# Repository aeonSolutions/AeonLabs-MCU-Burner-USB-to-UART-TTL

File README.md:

[PCB-Prototyping-Catalogue](https://github.com/aeonSolutions/PCB-Prototyping-Catalogue)  >>  [DIY & Maker](https://github.com/aeonSolutions/PCB-Prototyping-Catalogue/blob/main/DIY-Maker/README.md)  >> MCU Burner USB to UART TTL

<p align="right">
 <a href="https://github-com.translate.goog/aeonSolutions/PCB-Prototyping-Catalogue/tree/main?_x_tr_sl=en&_x_tr_tl=pt&_x_tr_hl=en&_x_tr_pto=wapp">Change Language</a> <br>
Last update: 17-2-2024
</p>

<br />

# AeonLabs MCU Burner USB to UART TTL
This repo contains the KiCad files for the micro-USB to UART TTL PCB  or USB to USB for MCUs compatible with direct USB firmware download. This PCB can do firmware download on any AeonLabs PCB designs or any other PCB running at 3.3V or 5.0V.
Features voltage selection : 3.0V 250mA/500mA or 5.0V 500mA and automatic reset and automatic boot. It can fit an enclosure with dimensions of 35x35x4 mm

*Don't forget to LIKE , SHARE and subscribe the free whatsApp group* and if you liked this PCB consider buying me a cup of coffee. Links below.

### Status
 Fully tested and working

<p align="center">
  <br>
 First Firmware download of AeonLabs's USB to UART TTL Burner
 </p>

## Revisions
- revision 1.4
  - added USB to USB option for MCUs compatible with direct USB firmware donwload
- revision 1.x
  - copper track bug corrections  
  - Voltage selection : 3.0V 250mA/500mA or 5.0V 500mA 
  - MCU firmware downloader with automatic reset and automatic boot. 

## Download options
Download this repository if you need the KiCad Files or, download the Gerber files in the release section of this repository

## Liked it ? Get a Free PCB for yourself
Send me your Device or hardware and i will design a custom PCB for it. Free of charge. Contact-me on WhatsApp or email for more info. 

## Q&A WhatsApp Group
If you have any Questions or simply  like this kind of projects and want to stay updated with the latest research ideas and prototypes during the day and week, join the WhatsApp Group
[LDAD Lab & Prototyping](https://chat.whatsapp.com/FkNC7u83kuy2QRA5sqjBVg)

There are useful answers on stackExchage about this topic i recommed reading. One is [ESP-WROOM-32 layout USB-UART](https://electronics.stackexchange.com/questions/429812/esp-wroom-32-layout-usb-uart/601827#601827) and [ESP32 with FTDI programmer](https://electronics.stackexchange.com/questions/448187/esp32-with-ftdi-programmer/601761#601761)

## Fully assembled PCB
### alternatively, and if you do not want to build a PCB by yourself, you can buy here:

The price will be around 30eur plus postage fees.
(I will also deliver the assembled PCB with all the components in place at a fair aditonal cost).
#### Be supportive of my dedication and work towards technology education and buy me a coffee. Link below.

## PCB Parts list
- DC2DC converter HX4002B x2 : https://s.click.aliexpress.com/e/_Ak7IPx
- Capacitor 100nF SMD 1206 : https://s.click.aliexpress.com/e/_AVdmzr
- Capacitor 2.2uF SMD 1206 : https://s.click.aliexpress.com/e/_AVdmzr
- LED SMD 1206 : https://s.click.aliexpress.com/e/_A9THIl
- Resistor SMD 1206 330R : https://s.click.aliexpress.com/e/_A7OXrR
- Programmer Clip : https://s.click.aliexpress.com/e/_A7s5EN
- 6 core wire : https://s.click.aliexpress.com/e/_Atht2d
- Micro USB PCB socket : https://s.click.aliexpress.com/e/_A123KH 

<br />
<br />

## Author

You can get in touch with me on my LinkedIn Profile:

#### Miguel Tomas

You can also follow my GitHub Profile to stay updated about my latest projects: 

<br>

**Hire me** <br>
See [here](https://github.com/aeonSolutions/PCB-Prototyping-Catalogue/wiki/How-to-Hire-AeonLabs) how to hire AeonLabs.

<br>

### Be supportive of my dedication and work towards technology education and buy me a cup of coffee
The PCB design Files I provide here for anyone to use are free. If you like this Smart Device or use it, please consider buying me a cup of coffee, a slice of pizza or a book to help me study, eat and think new PCB design files.

<p align="center">
    
</p>

### Make a donation on PayPal
Make a donation on PayPal and get a TAX refund*.

<p align="center">
    
</p>

### Support all these open hardware projects and become a GitHub sponsor  
Liked any of my PCB KiCad Designs? Help and Support my open work to all by becoming a GitHub sponsor.

<p align="center">

</p>

# 

### License

Before proceeding to download any of AeonLabs software solutions for open-source development and/or PCB hardware electronics development make sure you are choosing the right license for your project. See [AeonLabs Solutions for Open Hardware & Source Development](https://github.com/aeonSolutions/PCB-Prototyping-Catalogue/wiki/AeonLabs-Solutions-for-Open-Hardware-&-Source-Development) for more information.

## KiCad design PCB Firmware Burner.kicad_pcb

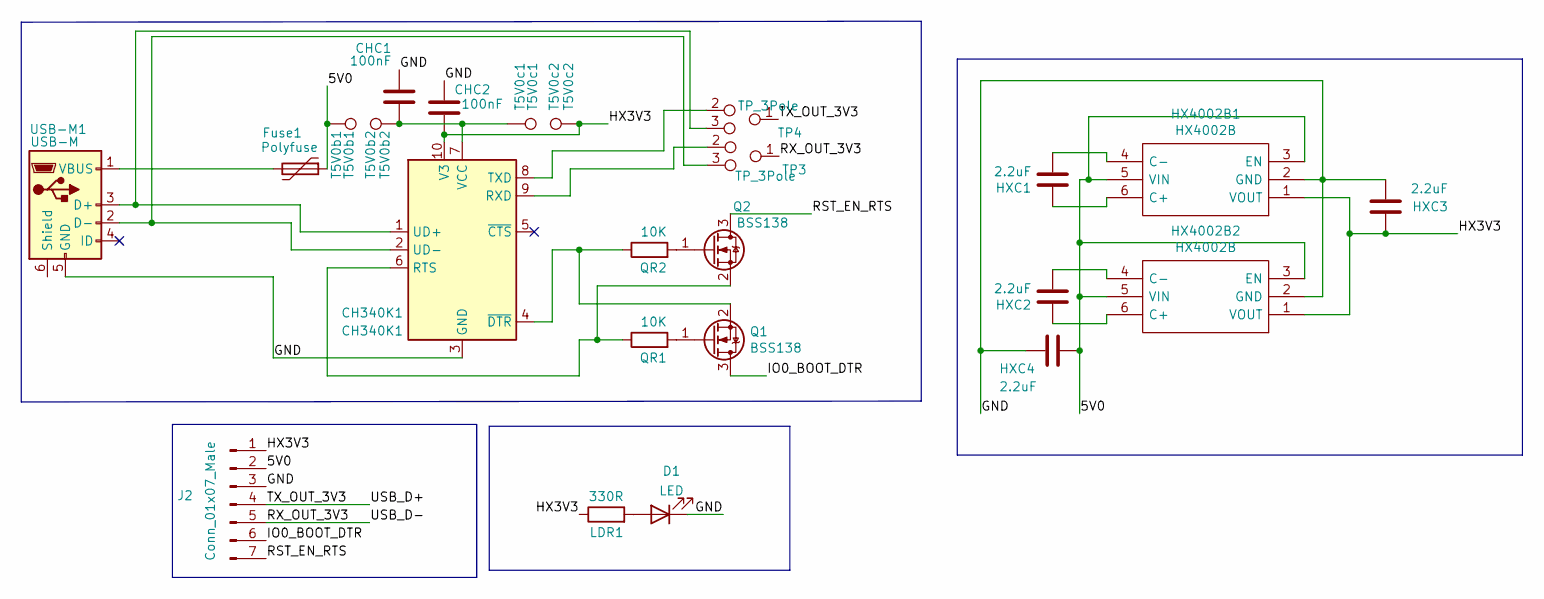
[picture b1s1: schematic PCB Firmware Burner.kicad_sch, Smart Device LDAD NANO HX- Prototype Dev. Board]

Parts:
CH340K1: CH340K1; SSOP-10_3.9x4.9mm_P1.00mm
CHC1, CHC2: 100nF; C_1206_3216Metric
D1: LED; LED_1206_3216Metric
Fuse1: Polyfuse; Fuse_1206_3216Metric
HX4002B1, HX4002B2: HX4002B; HX4002 SOT95 P280X125-6N; Manufacturer_Part_Number HX4002
HXC1, HXC2, HXC3, HXC4: 2.2uF; C_1206_3216Metric
J2: Conn_01x07_Male; PinHeader_1x07_P2.54mm_Horizontal
LDR1: 330R; R_0805_2012Metric_Pad1.20x1.40mm_HandSolder
Q1, Q2: BSS138; SOT-23
QR1, QR2: 10K; R_0805_2012Metric_Pad1.20x1.40mm_HandSolder
T5V0b1: T5V0b1; TestPoint_Pad_2.0x2.0mm
T5V0b2: T5V0b2; TestPoint_Pad_2.0x2.0mm
T5V0c1: T5V0c1; TestPoint_Pad_2.0x2.0mm
T5V0c2: T5V0c2; TestPoint_Pad_2.0x2.0mm
TP3, TP4: TP_3Pole; TestPoint_Pad_1.5mm 3 points
USB-M1: USB-M; Micro_USB_pcb_socket_5pin_4weld_points

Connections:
/5V0: Fuse1.1, HX4002B1.3 (EN), HX4002B1.5 (VIN), HX4002B2.3 (EN), HX4002B2.5 (VIN), HXC4.1, J2.2, T5V0b1.1
/GND: CH340K1.3 (GND), CHC1.2, CHC2.2, D1.1 (K), HX4002B1.2 (GND), HX4002B2.2 (GND), HXC3.2, HXC4.2, J2.3, USB-M1.5 (GND)
/HX3V3: CH340K1.10 (V3), CHC2.1, HX4002B1.1 (VOUT), HX4002B2.1 (VOUT), HXC3.1, J2.1, LDR1.1, T5V0c2.1
/IO0_BOOT_DTR: J2.6, Q1.3 (D)
/RST_EN_RTS: J2.7, Q2.3 (D)
/RX_OUT_3V3: J2.5, TP3.1
/TX_OUT_3V3: J2.4, TP4.1
unnamed: CH340K1.2 (UD-), TP3.3, USB-M1.2 (D-)
unnamed: CH340K1.4 (~DTR), Q1.2 (S), QR2.1
unnamed: CH340K1.6 (RTS), Q2.2 (S), QR1.1
unnamed: CH340K1.7 (VCC), CHC1.1, T5V0b2.1, T5V0c1.1
unnamed: CH340K1.8 (TXD), TP4.2
unnamed: CH340K1.9 (RXD), TP3.2
unnamed: D1.2 (A), LDR1.2
unnamed: Fuse1.2, USB-M1.1 (VBUS)
unnamed: HX4002B1.4 (C-), HXC1.2
unnamed: HX4002B1.6 (C+), HXC1.1
unnamed: HX4002B2.4 (C-), HXC2.2
unnamed: HX4002B2.6 (C+), HXC2.1
unnamed: Q1.1 (G), QR1.2
unnamed: Q2.1 (G), QR2.2
unnamed: CH340K1.1 (UD+), TP4.3, USB-M1.3 (D+)

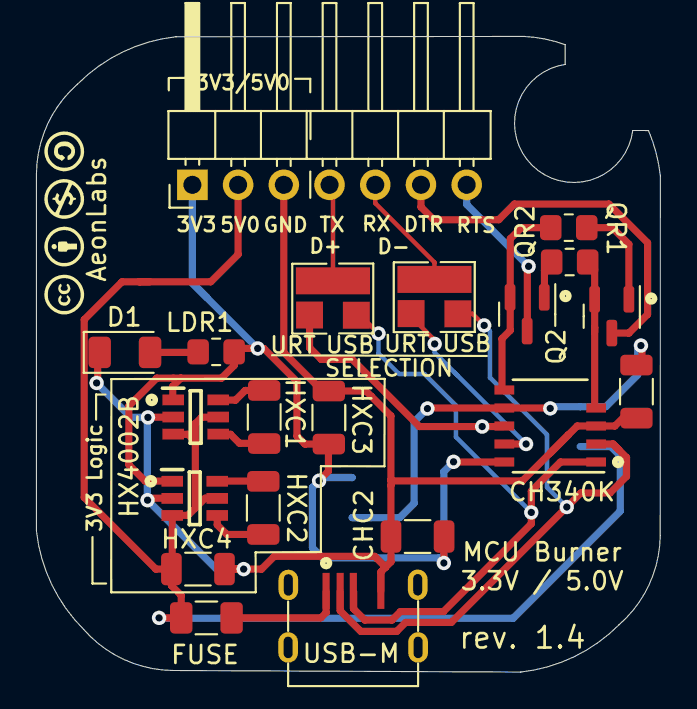
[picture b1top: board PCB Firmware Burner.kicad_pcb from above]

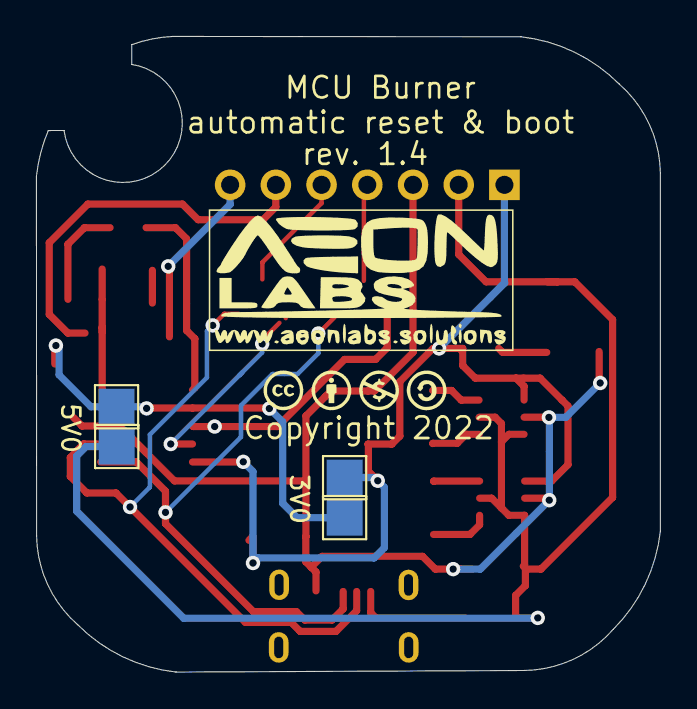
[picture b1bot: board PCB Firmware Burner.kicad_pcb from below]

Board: 2 copper layers, 34.7 x 35.3 mm, 24 parts (4 on the bottom side), 22 nets.

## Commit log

2022-03-28 first upload
2022-03-28 designs
2022-03-30 revision 1.1
2022-03-30 revision 1.2
    possibility of voltage selection: 3V3 or 5V0
2022-05-28 revision 1,3
    Track bug corrections
2022-07-05 smaller size
2022-08-05 rev 1.4

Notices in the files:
PCB Firmware Burner.kicad_pcb:
Copyright 2022
